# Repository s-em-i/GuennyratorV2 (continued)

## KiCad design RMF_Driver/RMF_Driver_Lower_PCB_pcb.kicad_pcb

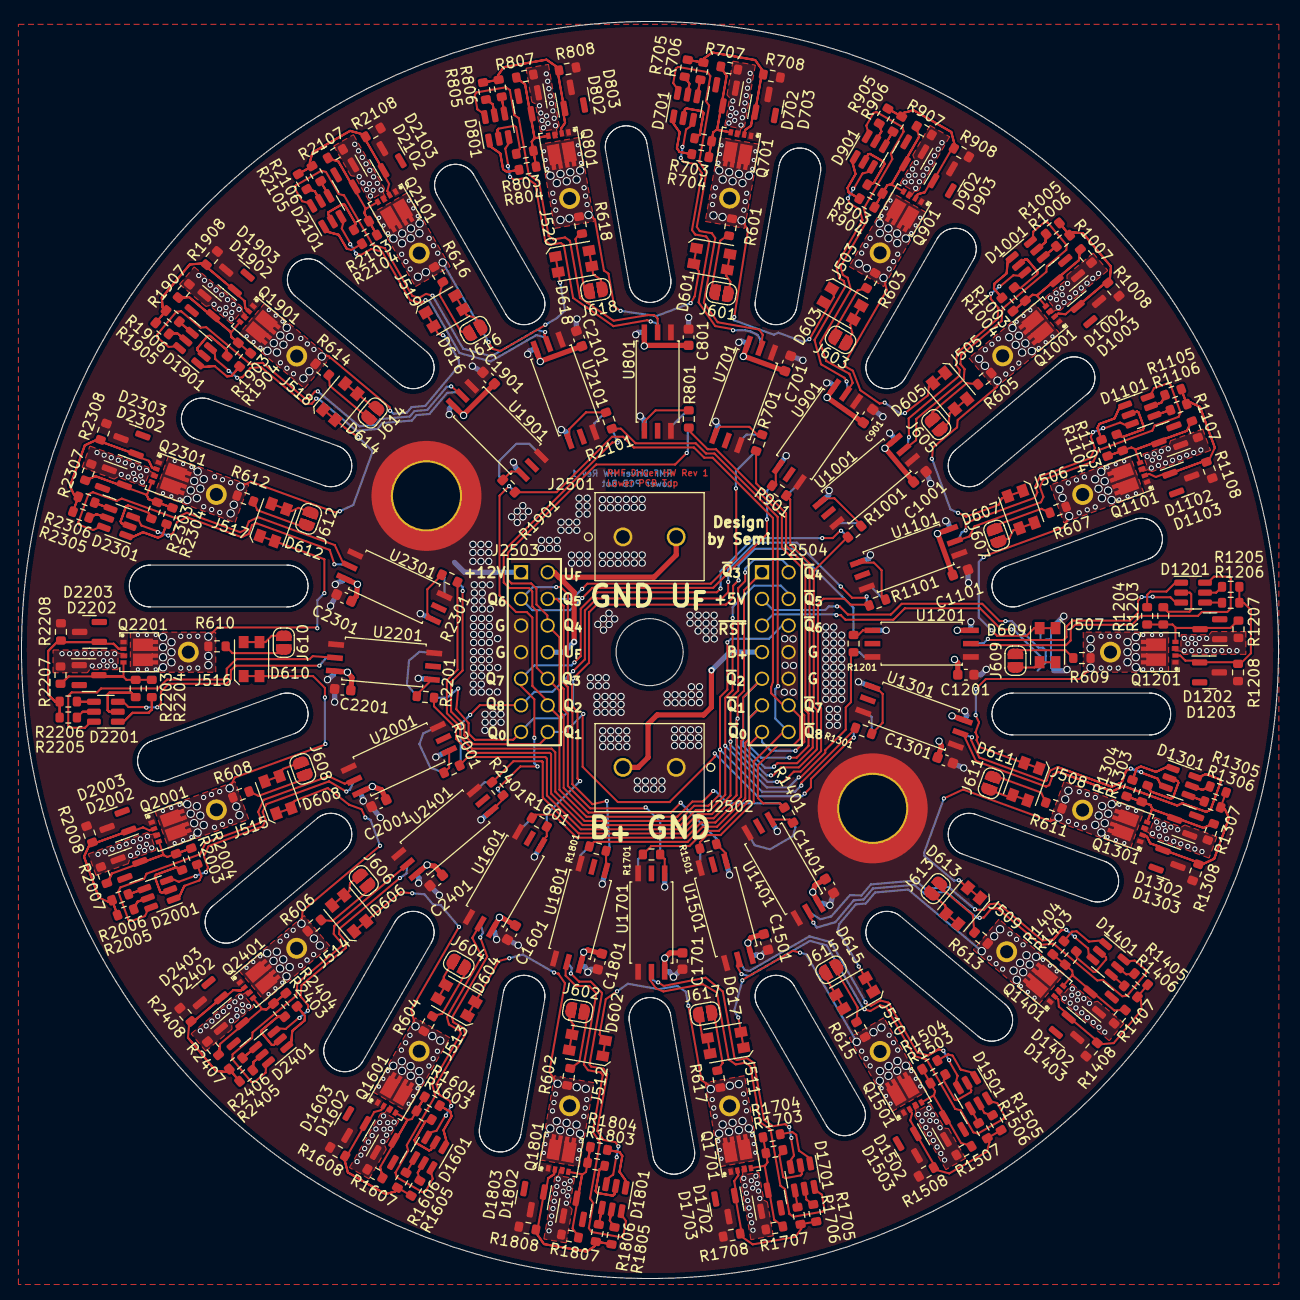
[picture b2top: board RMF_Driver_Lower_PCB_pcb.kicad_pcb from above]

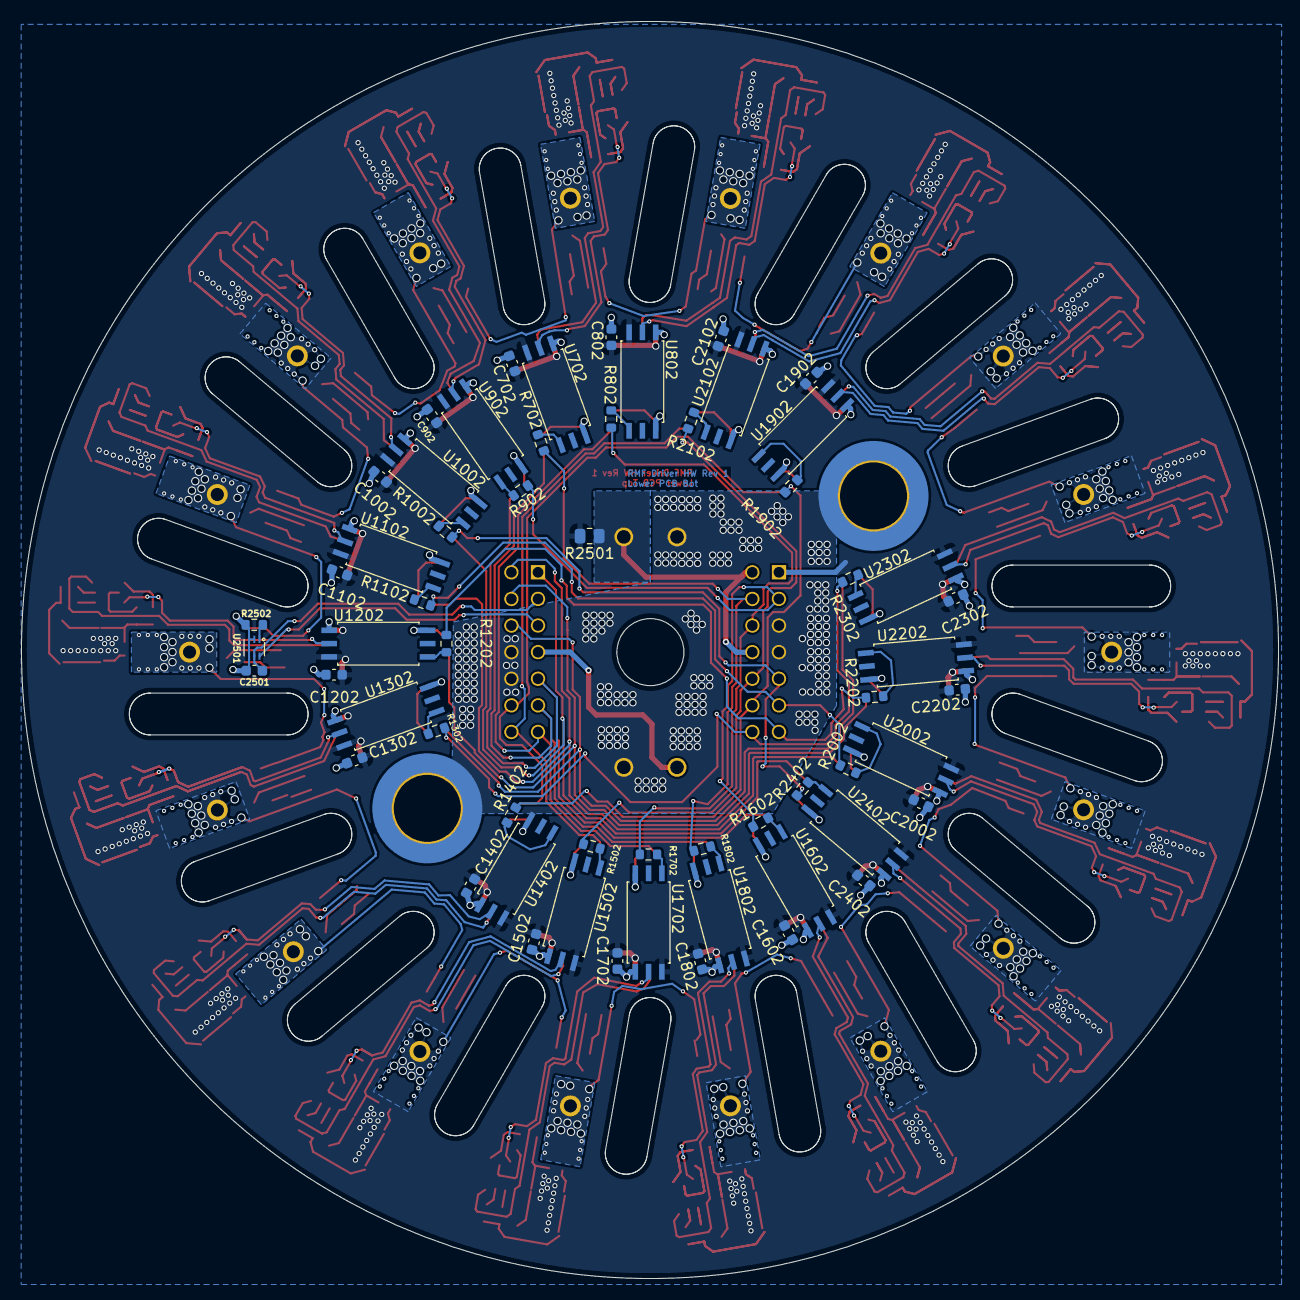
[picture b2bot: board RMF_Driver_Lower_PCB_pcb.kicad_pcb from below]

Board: 2 copper layers, 120.0 x 120.0 mm, 370 parts (58 on the bottom side), 259 nets.

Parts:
C701, C702, C801, C802, C901, C902, C1001, C1002, C1101, C1102, C1201, C1202, C1301, C1302, C1401, C1402, C1501, C1502, C1601, C1602, C1701, C1702, C1801, C1802, C1901, C1902, C2001, C2002, C2101, C2102, C2201, C2202, C2301, C2302, C2401, C2402, C2501: 100n; C_0603_1608Metric
D601, D602, D603, D604, D605, D606, D607, D608, D609, D610, D611, D612, D613, D614, D615, D616, D617, D618: LED; 150141SV73110
D701, D801, D901, D1001, D1101, D1201, D1301, D1401, D1501, D1601, D1701, D1801, D1901, D2001, D2101, D2201, D2301, D2401: SDM10M45SD; SOT-23-6
D702, D703, D802, D803, D902, D903, D1002, D1003, D1102, D1103, D1202, D1203, D1302, D1303, D1402, D1403, D1502, D1503, D1602, D1603, D1702, D1703, D1802, D1803, D1902, D1903, D2002, D2003, D2102, D2103, D2202, D2203, D2302, D2303, D2402, D2403: SZBZX84C15LT3G; SOT-23
H2501, H2502: MountingHole_Pad; MountingHole_6.4mm_M6_ISO7380_Pad_TopBottom
J502, J503, J505, J506, J507, J508, J509, J510, J511, J512, J513, J514, J515, J516, J517, J518, J519, J520: 243-131
J601, J602, J603, J604, J605, J606, J607, J608, J609, J610, J611, J612, J613, J614, J615, J616, J617, J618: Conn_01x02; SolderJumper-2_P1.3mm_Open_RoundedPad1.0x1.5mm
J2501, J2502: Screw_Terminal_01x02; 1729128
J2503, J2504: Socket_02x07; SAMTEC_SSW-107-01-G-D
Q701, Q801, Q901, Q1001, Q1101, Q1201, Q1301, Q1401, Q1501, Q1601, Q1701, Q1801, Q1901, Q2001, Q2101, Q2201, Q2301, Q2401: DMC3025LDV; Diodes_PowerDI3333-8_TypeUXC
R601, R602, R603, R604, R605, R606, R607, R608, R609, R610, R611, R612, R613, R614, R615, R616, R617, R618, R703, R706, R803, R806, R903, R906, R1003, R1006, R1103, R1106, R1203, R1206, R1303, R1306, R1403, R1406, R1503, R1506, R1603, R1606, R1703, R1706, R1803, R1806, R1903, R1906, R2003, R2006, R2103, R2106, R2203, R2206, R2303, R2306, R2403, R2406: 50; R_0603_1608Metric
R701, R702, R801, R802, R901, R902, R1001, R1002, R1101, R1102, R1201, R1202, R1301, R1302, R1401, R1402, R1501, R1502, R1601, R1602, R1701, R1702, R1801, R1802, R1901, R1902, R2001, R2002, R2101, R2102, R2201, R2202, R2301, R2302, R2401, R2402: 1.18k; R_0603_1608Metric
R704, R705, R804, R805, R904, R905, R1004, R1005, R1104, R1105, R1204, R1205, R1304, R1305, R1404, R1405, R1504, R1505, R1604, R1605, R1704, R1705, R1804, R1805, R1904, R1905, R2004, R2005, R2104, R2105, R2204, R2205, R2304, R2305, R2404, R2405: 20; R_0603_1608Metric
R707, R708, R807, R808, R907, R908, R1007, R1008, R1107, R1108, R1207, R1208, R1307, R1308, R1407, R1408, R1507, R1508, R1607, R1608, R1707, R1708, R1807, R1808, R1907, R1908, R2007, R2008, R2107, R2108, R2207, R2208, R2307, R2308, R2407, R2408: 100k; R_0603_1608Metric
R2501: 5m; R_0805_2012Metric
R2502: 88.7k; R_0603_1608Metric
U701, U702, U801, U802, U901, U902, U1001, U1002, U1101, U1102, U1201, U1202, U1301, U1302, U1401, U1402, U1501, U1502, U1601, U1602, U1701, U1702, U1801, U1802, U1901, U1902, U2001, U2002, U2101, U2102, U2201, U2202, U2301, U2302, U2401, U2402: TLP5772
U2501: TMP390A3DRLT

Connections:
+5V: C2501.1, J2504.03 (Pin_3), U2501.5 (VDD)
+12V: C701.1, C702.1, C801.1, C802.1, C901.1, C902.1, C1001.1, C1002.1, C1101.1, C1102.1, C1201.1, C1202.1, C1301.1, C1302.1, C1401.1, C1402.1, C1501.1, C1502.1, C1601.1, C1602.1, C1701.1, C1702.1, C1801.1, C1802.1, C1901.1, C1902.1, C2001.1, C2002.1, C2101.1, C2102.1, C2201.1, C2202.1, C2301.1, C2302.1, C2401.1, C2402.1, D702.1 (A), D802.1 (A), D902.1 (A), D1002.1 (A), D1102.1 (A), D1202.1 (A), D1302.1 (A), D1402.1 (A), D1502.1 (A), D1602.1 (A), D1702.1 (A), D1802.1 (A), D1902.1 (A), D2002.1 (A), D2102.1 (A), D2202.1 (A), D2302.1 (A), D2402.1 (A), J2503.01 (Pin_1), Q701.3 (S2), Q801.3 (S2), Q901.3 (S2), Q1001.3 (S2), Q1101.3 (S2), Q1201.3 (S2), Q1301.3 (S2), Q1401.3 (S2), Q1501.3 (S2), Q1601.3 (S2), Q1701.3 (S2), Q1801.3 (S2), Q1901.3 (S2), Q2001.3 (S2), Q2101.3 (S2), Q2201.3 (S2), Q2301.3 (S2), Q2401.3 (S2), R707.2, R807.2, R907.2, R1007.2, R1107.2, R1207.2, R1307.2, R1407.2, R1507.2, R1607.2, R1707.2, R1807.2, R1907.2, R2007.2, R2107.2, R2207.2, R2307.2, R2407.2, R2501.2, U701.6 (VCC), U702.6 (VCC), U801.6 (VCC), U802.6 (VCC), U901.6 (VCC), U902.6 (VCC), U1001.6 (VCC), U1002.6 (VCC), U1101.6 (VCC), U1102.6 (VCC), U1201.6 (VCC), U1202.6 (VCC), U1301.6 (VCC), U1302.6 (VCC), U1401.6 (VCC), U1402.6 (VCC), U1501.6 (VCC), U1502.6 (VCC), U1601.6 (VCC), U1602.6 (VCC), U1701.6 (VCC), U1702.6 (VCC), U1801.6 (VCC), U1802.6 (VCC), U1901.6 (VCC), U1902.6 (VCC), U2001.6 (VCC), U2002.6 (VCC), U2101.6 (VCC), U2102.6 (VCC), U2201.6 (VCC), U2202.6 (VCC), U2301.6 (VCC), U2302.6 (VCC), U2401.6 (VCC), U2402.6 (VCC)
B_{+}: J2502.2, J2504.07 (Pin_7)
GND: C701.2, C702.2, C801.2, C802.2, C901.2, C902.2, C1001.2, C1002.2, C1101.2, C1102.2, C1201.2, C1202.2, C1301.2, C1302.2, C1401.2, C1402.2, C1501.2, C1502.2, C1601.2, C1602.2, C1701.2, C1702.2, C1801.2, C1802.2, C1901.2, C1902.2, C2001.2, C2002.2, C2101.2, C2102.2, C2201.2, C2202.2, C2301.2, C2302.2, C2401.2, C2402.2, C2501.2, D703.3 (K), D803.3 (K), D903.3 (K), D1003.3 (K), D1103.3 (K), D1203.3 (K), D1303.3 (K), D1403.3 (K), D1503.3 (K), D1603.3 (K), D1703.3 (K), D1803.3 (K), D1903.3 (K), D2003.3 (K), D2103.3 (K), D2203.3 (K), D2303.3 (K), D2403.3 (K), H2501.1, H2502.1, J2501.1, J2502.1, J2503.05 (Pin_5), J2503.07 (Pin_7), J2504.08 (Pin_8), J2504.10, Q701.1 (S1), Q801.1 (S1), Q901.1 (S1), Q1001.1 (S1), Q1101.1 (S1), Q1201.1 (S1), Q1301.1 (S1), Q1401.1 (S1), Q1501.1 (S1), Q1601.1 (S1), Q1701.1 (S1), Q1801.1 (S1), Q1901.1 (S1), Q2001.1 (S1), Q2101.1 (S1), Q2201.1 (S1), Q2301.1 (S1), Q2401.1 (S1), R708.1, R808.1, R908.1, R1008.1, R1108.1, R1208.1, R1308.1, R1408.1, R1508.1, R1608.1, R1708.1, R1808.1, R1908.1, R2008.1, R2108.1, R2208.1, R2308.1, R2408.1, R2502.2, U701.3 (CATHODE), U701.4 (GND), U702.3 (CATHODE), U702.4 (GND), U801.3 (CATHODE), U801.4 (GND), U802.3 (CATHODE), U802.4 (GND), U901.3 (CATHODE), U901.4 (GND), U902.3 (CATHODE), U902.4 (GND), U1001.3 (CATHODE), U1001.4 (GND), U1002.3 (CATHODE), U1002.4 (GND), U1101.3 (CATHODE), U1101.4 (GND), U1102.3 (CATHODE), U1102.4 (GND), U1201.3 (CATHODE), U1201.4 (GND), U1202.3 (CATHODE), U1202.4 (GND), U1301.3 (CATHODE), U1301.4 (GND), U1302.3 (CATHODE), U1302.4 (GND), U1401.3 (CATHODE), U1401.4 (GND), U1402.3 (CATHODE), U1402.4 (GND), U1501.3 (CATHODE), U1501.4 (GND), U1502.3 (CATHODE), U1502.4 (GND), U1601.3 (CATHODE), U1601.4 (GND), U1602.3 (CATHODE), U1602.4 (GND), U1701.3 (CATHODE), U1701.4 (GND), U1702.3 (CATHODE), U1702.4 (GND), U1801.3 (CATHODE), U1801.4 (GND), U1802.3 (CATHODE), U1802.4 (GND), U1901.3 (CATHODE), U1901.4 (GND), U1902.3 (CATHODE), U1902.4 (GND), U2001.3 (CATHODE), U2001.4 (GND), U2002.3 (CATHODE), U2002.4 (GND), U2101.3 (CATHODE), U2101.4 (GND), U2102.3 (CATHODE), U2102.4 (GND), U2201.3 (CATHODE), U2201.4 (GND), U2202.3 (CATHODE), U2202.4 (GND), U2301.3 (CATHODE), U2301.4 (GND), U2302.3 (CATHODE), U2302.4 (GND), U2401.3 (CATHODE), U2401.4 (GND), U2402.3 (CATHODE), U2402.4 (GND), U2501.2 (SETB), U2501.3 (GND), U2501.4 (OUTB)
L_{0}-L_{1}: D603.3 (K), D603.4 (A), J502.1, Q701.5 (D2), Q701.8 (D1), R601.2
L_{1}-L_{2}: D605.3 (K), D605.4 (A), J503.1, Q901.5 (D2), Q901.8 (D1), R603.2
L_{2}-L_{3}: D607.3 (K), D607.4 (A), J505.1, Q1001.5 (D2), Q1001.8 (D1), R605.2
L_{3}-L_{4}: D609.3 (K), D609.4 (A), J506.1, Q1101.5 (D2), Q1101.8 (D1), R607.2
L_{4}-L_{5}: D611.3 (K), D611.4 (A), J507.1, Q1201.5 (D2), Q1201.8 (D1), R609.2
L_{5}-L_{6}: D613.3 (K), D613.4 (A), J508.1, Q1301.5 (D2), Q1301.8 (D1), R611.2
L_{6}-L_{7}: D615.3 (K), D615.4 (A), J509.1, Q1401.5 (D2), Q1401.8 (D1), R613.2
L_{7}-L_{8}: D617.3 (K), D617.4 (A), J510.1, Q1501.5 (D2), Q1501.8 (D1), R615.2
L_{8}-L_{9}: D602.3 (K), D602.4 (A), J511.1, Q1701.5 (D2), Q1701.8 (D1), R617.2
L_{9}-L_{10}: D604.3 (K), D604.4 (A), J512.1, Q1801.5 (D2), Q1801.8 (D1), R602.2
L_{10}-L_{11}: D606.3 (K), D606.4 (A), J513.1, Q1601.5 (D2), Q1601.8 (D1), R604.2
L_{11}-L_{12}: D608.3 (K), D608.4 (A), J514.1, Q2401.5 (D2), Q2401.8 (D1), R606.2
L_{12}-L_{13}: D610.3 (K), D610.4 (A), J515.1, Q2001.5 (D2), Q2001.8 (D1), R608.2
L_{13}-L_{14}: D612.3 (K), D612.4 (A), J516.1, Q2201.5 (D2), Q2201.8 (D1), R610.2
L_{14}-L_{15}: D614.3 (K), D614.4 (A), J517.1, Q2301.5 (D2), Q2301.8 (D1), R612.2
L_{15}-L_{16}: D616.3 (K), D616.4 (A), J518.1, Q1901.5 (D2), Q1901.8 (D1), R614.2
L_{16}-L_{17}: D618.3 (K), D618.4 (A), J519.1, Q2101.5 (D2), Q2101.8 (D1), R616.2
L_{17}-L_{0}: D601.3 (K), D601.4 (A), J520.1, Q801.5 (D2), Q801.8 (D1), R618.2
unnamed: D701.1 (A1), R704.1
unnamed: D701.6 (AK1), U701.5 (VO)
unnamed: D701.2 (K1), R703.1
unnamed: D701.4 (A1), R706.1
unnamed: D701.3 (AK2), U702.5 (VO)
unnamed: D701.5 (K2), R705.1
unnamed: D702.3 (K), Q701.4 (G2), R703.2, R704.2, R707.1
unnamed: D703.1 (A), Q701.2 (G1), R705.2, R706.2, R708.2
unnamed: D801.1 (A1), R804.1
unnamed: D801.6 (AK1), U801.5 (VO)
unnamed: D801.2 (K1), R803.1
unnamed: D801.4 (A1), R806.1
unnamed: D801.3 (AK2), U802.5 (VO)
unnamed: D801.5 (K2), R805.1
unnamed: D802.3 (K), Q801.4 (G2), R803.2, R804.2, R807.1
unnamed: D803.1 (A), Q801.2 (G1), R805.2, R806.2, R808.2
unnamed: D901.1 (A1), R904.1
unnamed: D901.6 (AK1), U901.5 (VO)
unnamed: D901.2 (K1), R903.1
unnamed: D901.4 (A1), R906.1
unnamed: D901.3 (AK2), U902.5 (VO)
unnamed: D901.5 (K2), R905.1
unnamed: D902.3 (K), Q901.4 (G2), R903.2, R904.2, R907.1
unnamed: D903.1 (A), Q901.2 (G1), R905.2, R906.2, R908.2
unnamed: D1001.1 (A1), R1004.1
unnamed: D1001.6 (AK1), U1001.5 (VO)
unnamed: D1001.2 (K1), R1003.1
unnamed: D1001.4 (A1), R1006.1
unnamed: D1001.3 (AK2), U1002.5 (VO)
unnamed: D1001.5 (K2), R1005.1
unnamed: D1002.3 (K), Q1001.4 (G2), R1003.2, R1004.2, R1007.1
unnamed: D1003.1 (A), Q1001.2 (G1), R1005.2, R1006.2, R1008.2
unnamed: D1101.1 (A1), R1104.1
unnamed: D1101.6 (AK1), U1101.5 (VO)
unnamed: D1101.2 (K1), R1103.1
unnamed: D1101.4 (A1), R1106.1
unnamed: D1101.3 (AK2), U1102.5 (VO)
unnamed: D1101.5 (K2), R1105.1
unnamed: D1102.3 (K), Q1101.4 (G2), R1103.2, R1104.2, R1107.1
unnamed: D1103.1 (A), Q1101.2 (G1), R1105.2, R1106.2, R1108.2
unnamed: D1201.1 (A1), R1204.1
unnamed: D1201.6 (AK1), U1201.5 (VO)
unnamed: D1201.2 (K1), R1203.1
unnamed: D1201.4 (A1), R1206.1
unnamed: D1201.3 (AK2), U1202.5 (VO)
unnamed: D1201.5 (K2), R1205.1
unnamed: D1202.3 (K), Q1201.4 (G2), R1203.2, R1204.2, R1207.1
unnamed: D1203.1 (A), Q1201.2 (G1), R1205.2, R1206.2, R1208.2
unnamed: D1301.1 (A1), R1304.1
unnamed: D1301.6 (AK1), U1301.5 (VO)
unnamed: D1301.2 (K1), R1303.1
unnamed: D1301.4 (A1), R1306.1
unnamed: D1301.3 (AK2), U1302.5 (VO)
unnamed: D1301.5 (K2), R1305.1
unnamed: D1302.3 (K), Q1301.4 (G2), R1303.2, R1304.2, R1307.1
unnamed: D1303.1 (A), Q1301.2 (G1), R1305.2, R1306.2, R1308.2
unnamed: D1401.1 (A1), R1404.1
unnamed: D1401.6 (AK1), U1401.5 (VO)
unnamed: D1401.2 (K1), R1403.1
unnamed: D1401.4 (A1), R1406.1
unnamed: D1401.3 (AK2), U1402.5 (VO)
unnamed: D1401.5 (K2), R1405.1
unnamed: D1402.3 (K), Q1401.4 (G2), R1403.2, R1404.2, R1407.1
unnamed: D1403.1 (A), Q1401.2 (G1), R1405.2, R1406.2, R1408.2
unnamed: D1501.1 (A1), R1504.1
unnamed: D1501.6 (AK1), U1501.5 (VO)
unnamed: D1501.2 (K1), R1503.1
unnamed: D1501.4 (A1), R1506.1
unnamed: D1501.3 (AK2), U1502.5 (VO)
unnamed: D1501.5 (K2), R1505.1
unnamed: D1502.3 (K), Q1501.4 (G2), R1503.2, R1504.2, R1507.1
unnamed: D1503.1 (A), Q1501.2 (G1), R1505.2, R1506.2, R1508.2
unnamed: D1601.1 (A1), R1604.1
unnamed: D1601.6 (AK1), U1601.5 (VO)
unnamed: D1601.2 (K1), R1603.1
unnamed: D1601.4 (A1), R1606.1
unnamed: D1601.3 (AK2), U1602.5 (VO)
unnamed: D1601.5 (K2), R1605.1
unnamed: D1602.3 (K), Q1601.4 (G2), R1603.2, R1604.2, R1607.1
unnamed: D1603.1 (A), Q1601.2 (G1), R1605.2, R1606.2, R1608.2
unnamed: D1701.1 (A1), R1704.1
unnamed: D1701.6 (AK1), U1701.5 (VO)
unnamed: D1701.2 (K1), R1703.1
unnamed: D1701.4 (A1), R1706.1
unnamed: D1701.3 (AK2), U1702.5 (VO)
unnamed: D1701.5 (K2), R1705.1
unnamed: D1702.3 (K), Q1701.4 (G2), R1703.2, R1704.2, R1707.1
unnamed: D1703.1 (A), Q1701.2 (G1), R1705.2, R1706.2, R1708.2
unnamed: D1801.1 (A1), R1804.1
unnamed: D1801.6 (AK1), U1801.5 (VO)
unnamed: D1801.2 (K1), R1803.1
unnamed: D1801.4 (A1), R1806.1
unnamed: D1801.3 (AK2), U1802.5 (VO)
unnamed: D1801.5 (K2), R1805.1
unnamed: D1802.3 (K), Q1801.4 (G2), R1803.2, R1804.2, R1807.1
unnamed: D1803.1 (A), Q1801.2 (G1), R1805.2, R1806.2, R1808.2
unnamed: D1901.1 (A1), R1904.1
unnamed: D1901.6 (AK1), U1901.5 (VO)
unnamed: D1901.2 (K1), R1903.1
unnamed: D1901.4 (A1), R1906.1
unnamed: D1901.3 (AK2), U1902.5 (VO)
unnamed: D1901.5 (K2), R1905.1
unnamed: D1902.3 (K), Q1901.4 (G2), R1903.2, R1904.2, R1907.1
unnamed: D1903.1 (A), Q1901.2 (G1), R1905.2, R1906.2, R1908.2
unnamed: D2001.1 (A1), R2004.1
unnamed: D2001.6 (AK1), U2001.5 (VO)
unnamed: D2001.2 (K1), R2003.1
unnamed: D2001.4 (A1), R2006.1
unnamed: D2001.3 (AK2), U2002.5 (VO)
unnamed: D2001.5 (K2), R2005.1
unnamed: D2002.3 (K), Q2001.4 (G2), R2003.2, R2004.2, R2007.1
unnamed: D2003.1 (A), Q2001.2 (G1), R2005.2, R2006.2, R2008.2
unnamed: D2101.1 (A1), R2104.1
unnamed: D2101.6 (AK1), U2101.5 (VO)
unnamed: D2101.2 (K1), R2103.1
unnamed: D2101.4 (A1), R2106.1
unnamed: D2101.3 (AK2), U2102.5 (VO)
unnamed: D2101.5 (K2), R2105.1
unnamed: D2102.3 (K), Q2101.4 (G2), R2103.2, R2104.2, R2107.1
unnamed: D2103.1 (A), Q2101.2 (G1), R2105.2, R2106.2, R2108.2
unnamed: D2201.1 (A1), R2204.1
unnamed: D2201.6 (AK1), U2201.5 (VO)
unnamed: D2201.2 (K1), R2203.1
unnamed: D2201.4 (A1), R2206.1
unnamed: D2201.3 (AK2), U2202.5 (VO)
unnamed: D2201.5 (K2), R2205.1
unnamed: D2202.3 (K), Q2201.4 (G2), R2203.2, R2204.2, R2207.1
unnamed: D2203.1 (A), Q2201.2 (G1), R2205.2, R2206.2, R2208.2
unnamed: D2301.1 (A1), R2304.1
unnamed: D2301.6 (AK1), U2301.5 (VO)
unnamed: D2301.2 (K1), R2303.1
unnamed: D2301.4 (A1), R2306.1
unnamed: D2301.3 (AK2), U2302.5 (VO)
unnamed: D2301.5 (K2), R2305.1
unnamed: D2302.3 (K), Q2301.4 (G2), R2303.2, R2304.2, R2307.1
unnamed: D2303.1 (A), Q2301.2 (G1), R2305.2, R2306.2, R2308.2
unnamed: D2401.1 (A1), R2404.1
unnamed: D2401.6 (AK1), U2401.5 (VO)
unnamed: D2401.2 (K1), R2403.1
unnamed: D2401.4 (A1), R2406.1
unnamed: D2401.3 (AK2), U2402.5 (VO)
unnamed: D2401.5 (K2), R2405.1
unnamed: D2402.3 (K), Q2401.4 (G2), R2403.2, R2404.2, R2407.1
unnamed: D2403.1 (A), Q2401.2 (G1), R2405.2, R2406.2, R2408.2
unnamed: J601.1, R601.1
unnamed: D601.1 (A), D601.2 (K), J601.2
unnamed: J602.1, R602.1
unnamed: D602.1 (A), D602.2 (K), J602.2
unnamed: J603.1, R603.1
unnamed: D603.1 (A), D603.2 (K), J603.2
unnamed: J604.1, R604.1
unnamed: D604.1 (A), D604.2 (K), J604.2
unnamed: J605.1, R605.1
unnamed: D605.1 (A), D605.2 (K), J605.2
unnamed: J606.1, R606.1
unnamed: D606.1 (A), D606.2 (K), J606.2
unnamed: J607.1, R607.1
unnamed: D607.1 (A), D607.2 (K), J607.2
unnamed: J608.1, R608.1
unnamed: D608.1 (A), D608.2 (K), J608.2
unnamed: J609.1, R609.1
unnamed: D609.1 (A), D609.2 (K), J609.2
unnamed: J610.1, R610.1
unnamed: D610.1 (A), D610.2 (K), J610.2
unnamed: J611.1, R611.1
unnamed: D611.1 (A), D611.2 (K), J611.2
unnamed: J612.1, R612.1
unnamed: D612.1 (A), D612.2 (K), J612.2
unnamed: J613.1, R613.1
unnamed: D613.1 (A), D613.2 (K), J613.2
unnamed: J614.1, R614.1
unnamed: D614.1 (A), D614.2 (K), J614.2
unnamed: J615.1, R615.1
unnamed: D615.1 (A), D615.2 (K), J615.2
unnamed: J616.1, R616.1
unnamed: D616.1 (A), D616.2 (K), J616.2
unnamed: J617.1, R617.1
unnamed: D617.1 (A), D617.2 (K), J617.2
unnamed: J618.1, R618.1
unnamed: D618.1 (A), D618.2 (K), J618.2
unnamed: R701.1, U701.1 (ANODE)
unnamed: R702.1, U702.1 (ANODE)
unnamed: R801.1, U801.1 (ANODE)
unnamed: R802.1, U802.1 (ANODE)
unnamed: R901.1, U901.1 (ANODE)
unnamed: R902.1, U902.1 (ANODE)
unnamed: R1001.1, U1001.1 (ANODE)
unnamed: R1002.1, U1002.1 (ANODE)
unnamed: R1101.1, U1101.1 (ANODE)
unnamed: R1102.1, U1102.1 (ANODE)
unnamed: R1201.1, U1201.1 (ANODE)
unnamed: R1202.1, U1202.1 (ANODE)
unnamed: R1301.1, U1301.1 (ANODE)
unnamed: R1302.1, U1302.1 (ANODE)
unnamed: R1401.1, U1401.1 (ANODE)
unnamed: R1402.1, U1402.1 (ANODE)
unnamed: R1501.1, U1501.1 (ANODE)
unnamed: R1502.1, U1502.1 (ANODE)
unnamed: R1601.1, U1601.1 (ANODE)
unnamed: R1602.1, U1602.1 (ANODE)
unnamed: R1701.1, U1701.1 (ANODE)
unnamed: R1702.1, U1702.1 (ANODE)
unnamed: R1801.1, U1801.1 (ANODE)
unnamed: R1802.1, U1802.1 (ANODE)
unnamed: R1901.1, U1901.1 (ANODE)
unnamed: R1902.1, U1902.1 (ANODE)
unnamed: R2001.1, U2001.1 (ANODE)
unnamed: R2002.1, U2002.1 (ANODE)
unnamed: R2101.1, U2101.1 (ANODE)
unnamed: R2102.1, U2102.1 (ANODE)
unnamed: R2201.1, U2201.1 (ANODE)
unnamed: R2202.1, U2202.1 (ANODE)
unnamed: R2301.1, U2301.1 (ANODE)
unnamed: R2302.1, U2302.1 (ANODE)
unnamed: R2401.1, U2401.1 (ANODE)
unnamed: R2402.1, U2402.1 (ANODE)
unnamed: R2502.1, U2501.1 (SETA)
Q_{0}^{^}: J2503.13, R1202.2, R2202.2
Q_{1}^{^}: J2503.14, R1302.2, R2302.2
Q_{2}^{^}: J2503.12, R1402.2, R1902.2
Q_{3}^{^}: J2503.10, R1502.2, R2102.2
Q_{4}^{^}: J2503.06 (Pin_6), R802.2, R1702.2
Q_{5}^{^}: J2503.04 (Pin_4), R702.2, R1802.2
Q_{6}^{^}: J2503.03 (Pin_3), R902.2, R1602.2
Q_{7}^{^}: J2503.09 (Pin_9), R1002.2, R2402.2
Q_{8}^{^}: J2503.11, R1102.2, R2002.2
U_{F}: J2501.2, J2503.02 (Pin_2), J2503.08 (Pin_8), R2501.1
~Q_{0}^{^}: J2504.13, R801.2, R1701.2
~Q_{1}^{^}: J2504.11, R701.2, R1801.2
~Q_{2}^{^}: J2504.09 (Pin_9), R901.2, R1601.2
~Q_{3}^{^}: J2504.01 (Pin_1), R1001.2, R2401.2
~Q_{4}^{^}: J2504.02 (Pin_2), R1101.2, R2001.2
~Q_{5}^{^}: J2504.04 (Pin_4), R1201.2, R2201.2
~Q_{6}^{^}: J2504.06 (Pin_6), R1301.2, R2301.2
~Q_{7}^{^}: J2504.12, R1401.2, R1901.2
~Q_{8}^{^}: J2504.14, R1501.2, R2101.2
~Reset^{^}: J2504.05 (Pin_5), U2501.6 (OUTA)
